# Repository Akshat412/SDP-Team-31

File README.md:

# SDP-Team-31
SDP23 Project for Team 31

We present SMH, a smart biking helmet and associated sensing system which can sense riders’ vital signs such as heart rate, ambient temperature and humidity, and make it accessible to them while they bike. In the event of an accident, the system would send a remote alert to a registered contact, including the rider’s location. The helmet uses a microcontroller for sampling a MEMS accelerometer capable of measuring upto 200 Gs of acceleration at 4 KHz for collision detection. In the event of a dangerous collision, the system communicates with an Android app over Bluetooth Low Energy, which then sends a text message to an emergency contact. The bike board samples temperature, humidity, heart rate, altitude and UV-index and displays them to the biker during their bike ride. Both devices are lightweight, inexpensive, and have long battery lives. 

Members: 
Marloon Paula Gonzalez - EE 2023; 
Max Morel - EE 2023; 
Ruchit Patel - EE 2023; 
Akshat Sahay - CompE 2023; 

This repository contains the hardware and software for the helmet board which performs concussion detection and generates BLE alerts for the associated smartphone app in case of a dangerous collision. Software is written using the RP2040 core in Arduino, with the Adafruit BLE Friend library to interface with the BLE module. The hardware is designed in KiCad 7.

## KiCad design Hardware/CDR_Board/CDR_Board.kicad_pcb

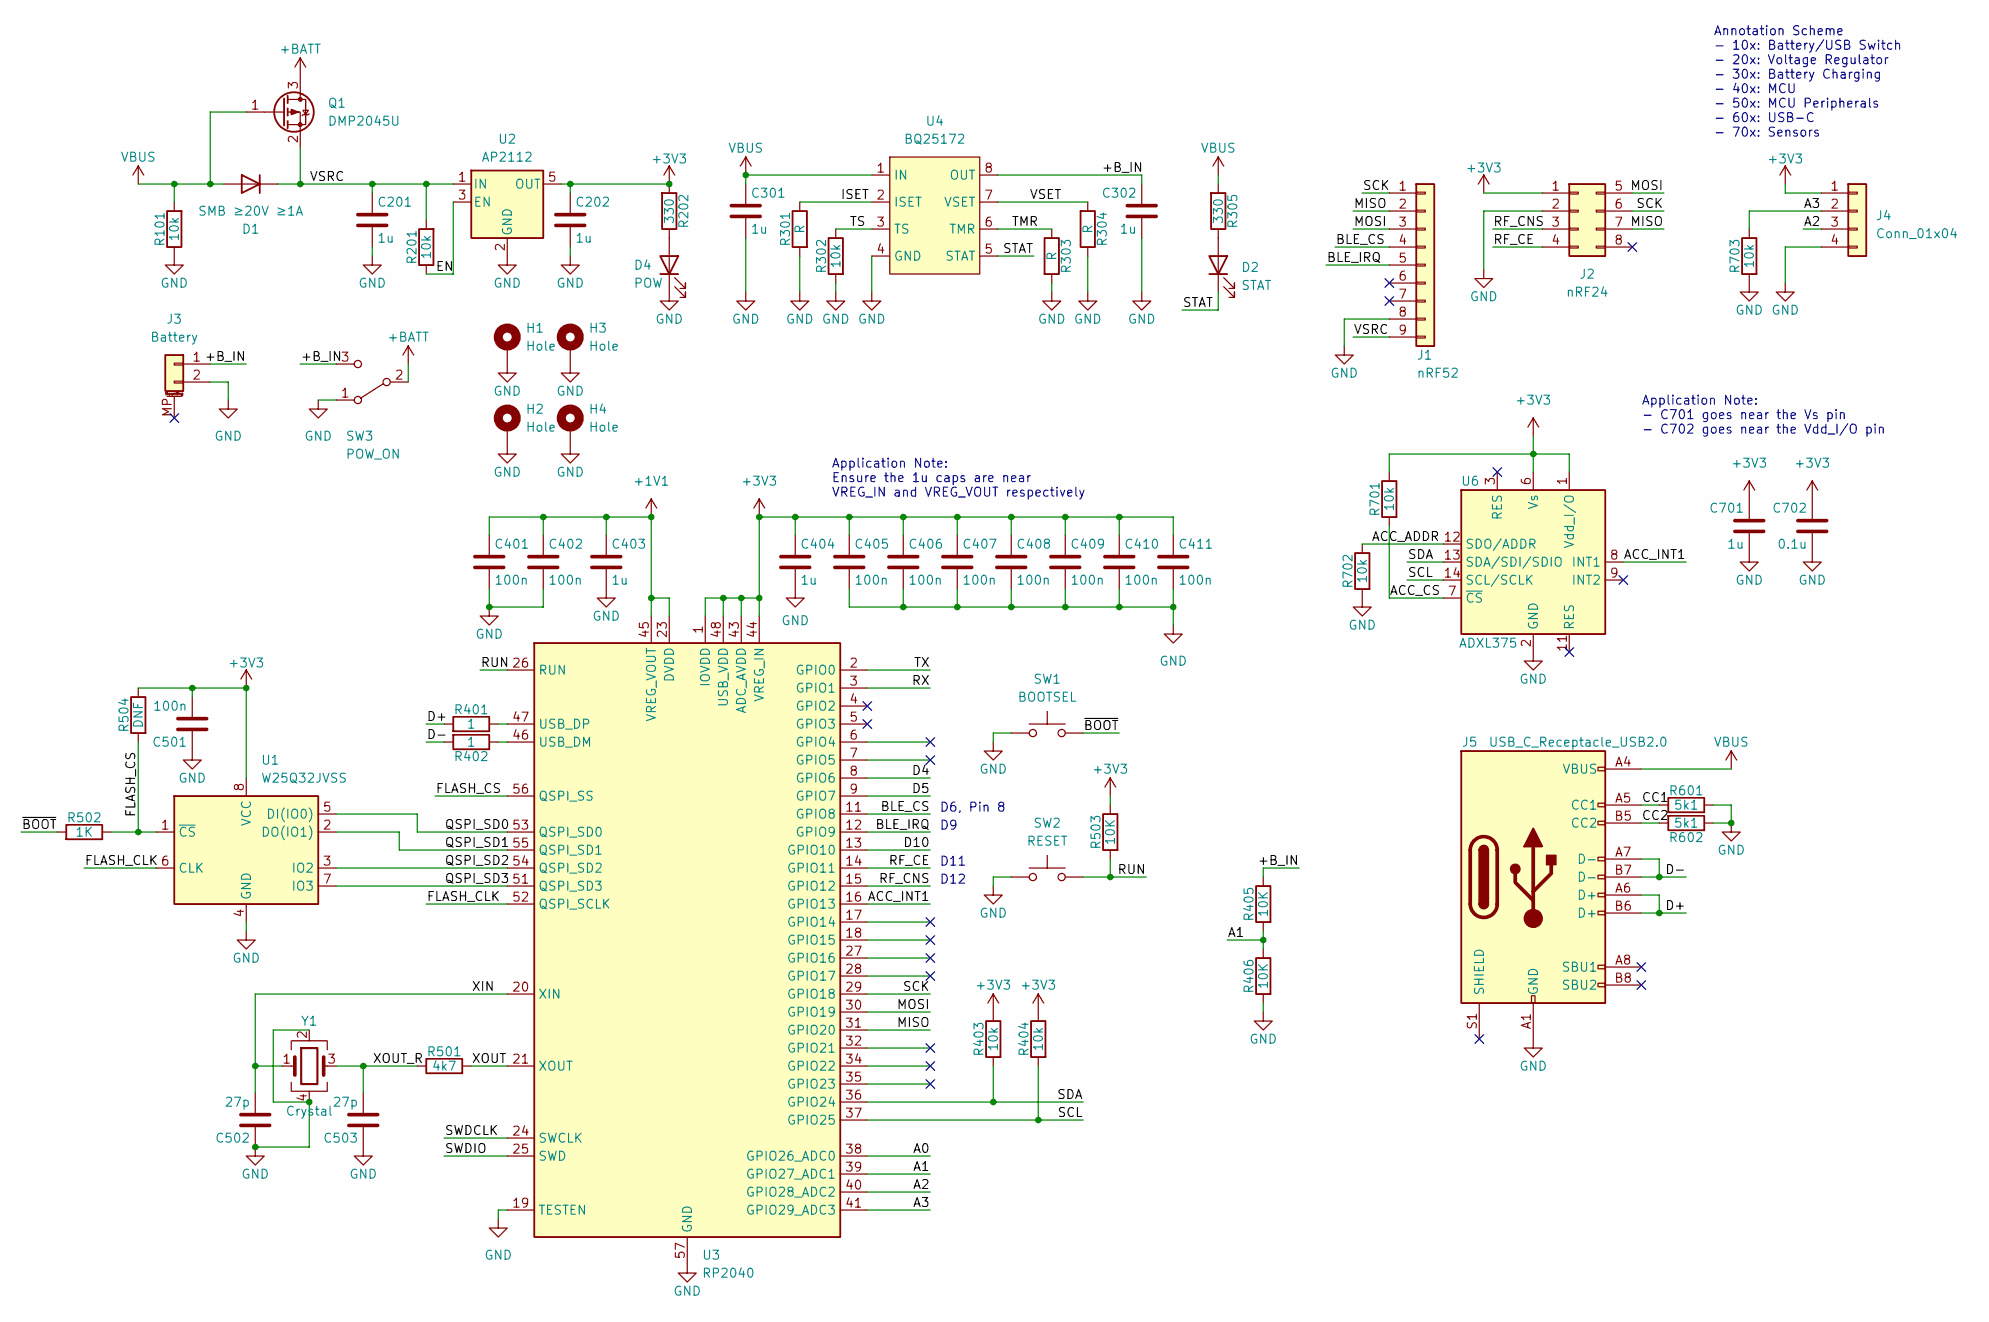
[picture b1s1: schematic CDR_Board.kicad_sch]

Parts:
C201, C202, C301, C302, C701: 1u; C_0805_2012Metric_Pad1.18x1.45mm_HandSolder
C401, C402, C405, C406, C407, C408, C409, C410, C411: 100n; C_0603_1608Metric_Pad1.08x0.95mm_HandSolder
C403, C404: 1u; C_0603_1608Metric_Pad1.08x0.95mm_HandSolder
C501: 100n; C_0805_2012Metric_Pad1.18x1.45mm_HandSolder
C502, C503: 27p; C_0805_2012Metric_Pad1.18x1.45mm_HandSolder
C702: 0.1u; C_0805_2012Metric_Pad1.18x1.45mm_HandSolder
D1: SMB ≥20V ≥1A; D_SOD-323_HandSoldering
D2: STAT; LED_0805_2012Metric_Pad1.15x1.40mm_HandSolder
D4: POW; LED_0805_2012Metric_Pad1.15x1.40mm_HandSolder
H1, H2, H3, H4: Hole; MountingHole_2.2mm_M2_DIN965_Pad
J1: nRF52; PinSocket_1x09_P2.54mm_Vertical
J2: nRF24; PinSocket_2x04_P2.54mm_Vertical
J3: Battery; JST_PH_S2B-PH-SM4-TB_1x02-1MP_P2.00mm_Horizontal
J4: Conn_01x04; PinSocket_1x04_P2.54mm_Vertical
J5: USB_C_Receptacle_USB2.0; USB_C_Receptacle_Palconn_UTC16-G
Q1: DMP2045U; SOT-23
R101, R201, R302, R403, R404, R701, R702, R703: 10k; R_0805_2012Metric_Pad1.20x1.40mm_HandSolder
R202, R305: 330; R_0805_2012Metric_Pad1.20x1.40mm_HandSolder
R301, R303, R304: R; R_0805_2012Metric_Pad1.20x1.40mm_HandSolder
R401, R402: 1; R_0805_2012Metric_Pad1.20x1.40mm_HandSolder
R405, R406, R503: 10K; R_0805_2012Metric_Pad1.20x1.40mm_HandSolder
R501: 4k7; R_0805_2012Metric_Pad1.20x1.40mm_HandSolder
R502: 1K; R_0805_2012Metric_Pad1.20x1.40mm_HandSolder
R504: DNF; R_0805_2012Metric_Pad1.20x1.40mm_HandSolder
R601, R602: 5k1; R_0805_2012Metric_Pad1.20x1.40mm_HandSolder
SW1: BOOTSEL; SW_Push_1P1T_NO_CK_KMR2
SW2: RESET; SW_Push_1P1T_NO_CK_KMR2
SW3: POW_ON; E-Switch-EG1218
U1: W25Q32JVSS; SOIC-8_5.23x5.23mm_P1.27mm
U2: AP2112; SOT-23-5
U3: RP2040; QFN-56-1EP_7x7mm_P0.4mm_EP3.2x3.2mm
U4: BQ25172; WSON-8-1EP_2x2mm_P0.5mm_EP0.9x1.6mm_ThermalVias
U6: ADXL375; LGA-14_3x5mm_P0.8mm_LayoutBorder1x6y
Y1: Crystal; Crystal_SMD_SeikoEpson_FA238-4Pin_3.2x2.5mm

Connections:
+1V1: C401.1, C402.1, C403.1, U3.23 (DVDD), U3.45 (VREG_VOUT), U3.50 (DVDD)
+3V3: C202.1, C404.1, C405.1, C406.1, C407.1, C408.1, C409.1, C410.1, C411.1, C501.2, C701.1, C702.1, J2.1, J4.1, R202.2, R403.1, R404.1, R503.1, R504.1, R701.1, U1.8 (VCC), U2.5 (OUT), U3.1 (IOVDD), U3.10 (IOVDD), U3.22 (IOVDD), U3.33 (IOVDD), U3.42 (IOVDD), U3.43 (ADC_AVDD), U3.44 (VREG_IN), U3.48 (USB_VDD), U3.49 (IOVDD), U6.1 (Vdd_I/O), U6.6 (Vs)
+BATT: Q1.3 (D), SW3.2 (B)
/+B_IN: C302.1, J3.1, R405.1, SW3.3 (C), U4.8 (OUT)
/A0: U3.38 (GPIO26_ADC0)
/A1: R405.2, R406.1, U3.39 (GPIO27_ADC1)
/A2: J4.3, U3.40 (GPIO28_ADC2)
/A3: J4.2, R703.1, U3.41 (GPIO29_ADC3)
/ACC_ADDR: R702.1, U6.12 (SDO/ADDR)
/ACC_CS: R701.2, U6.7 (~CS)
/ACC_INT1: U3.16 (GPIO13), U6.8 (INT1)
/BLE_CS: J1.4, U3.11 (GPIO8)
/BLE_IRQ: J1.5, U3.12 (GPIO9)
/CC1: J5.A5 (CC1), R601.2
/CC2: J5.B5 (CC2), R602.2
/D4: U3.8 (GPIO6)
/D5: U3.9 (GPIO7)
/D10: U3.13 (GPIO10)
/D+: J5.A6 (D+), J5.B6 (D+), R401.2
/D-: J5.A7 (D-), J5.B7 (D-), R402.2
/EN: R201.1, U2.3 (EN)
/FLASH_CLK: U1.6 (CLK), U3.52 (QSPI_SCLK)
/FLASH_CS: R502.1, R504.2, U1.1 (~CS), U3.56 (QSPI_SS)
/ISET: R301.1, U4.2 (ISET)
/MISO: J1.2, J2.7, U3.31 (GPIO20)
/MOSI: J1.3, J2.5, U3.30 (GPIO19)
/QSPI_SD0: U1.5 (DI(IO0)), U3.53 (QSPI_SD0)
/QSPI_SD1: U1.2 (DO(IO1)), U3.55 (QSPI_SD1)
/QSPI_SD2: U1.3 (IO2), U3.54 (QSPI_SD2)
/QSPI_SD3: U1.7 (IO3), U3.51 (QSPI_SD3)
/RF_CE: J2.4, U3.14 (GPIO11)
/RF_CNS: J2.3, U3.15 (GPIO12)
/RUN: R503.2, SW2.2, U3.26 (RUN)
/RX: U3.3 (GPIO1)
/SCK: J1.1, J2.6, U3.29 (GPIO18)
/SCL: R404.2, U3.37 (GPIO25), U6.14 (SCL/SCLK)
/SDA: R403.2, U3.36 (GPIO24), U6.13 (SDA/SDI/SDIO)
/STAT: D2.1 (K), U4.5 (STAT)
/SWDCLK: U3.24 (SWCLK)
/SWDIO: U3.25 (SWD)
/TMR: R303.1, U4.6 (TMR)
/TS: R302.1, U4.3 (TS)
/TX: U3.2 (GPIO0)
/VSET: R304.2, U4.7 (VSET)
/VSRC: C201.1, D1.1 (K), J1.9, Q1.2 (S), R201.2, U2.1 (IN)
/XIN: C502.2, U3.20 (XIN), Y1.1
/XOUT: R501.2, U3.21 (XOUT)
/XOUT_R: C503.2, R501.1, Y1.3
/~BOOT: R502.2, SW1.2
GND: C201.2, C202.2, C301.2, C302.2, C401.2, C402.2, C403.2, C404.2, C405.2, C406.2, C407.2, C408.2, C409.2, C410.2, C411.2, C501.1, C502.1, C503.1, C701.2, C702.2, D4.1 (K), H1.1, H2.1, H3.1, H4.1, J1.8, J2.2, J3.2, J4.4, J5.A1 (GND), J5.A12 (GND), J5.B1 (GND), J5.B12 (GND), R101.1, R301.2, R302.2, R303.2, R304.1, R406.2, R601.1, R602.1, R702.2, R703.2, SW1.1, SW2.1, SW3.1 (A), U1.4 (GND), U2.2 (GND), U3.19 (TESTEN), U3.57 (GND), U4.4 (GND), U6.2 (GND), U6.4 (GND), U6.5 (GND), Y1.2, Y1.4
unnamed: D2.2 (A), R305.1
unnamed: D4.2 (A), R202.1
unnamed: R402.1, U3.46 (USB_DM)
unnamed: R401.1, U3.47 (USB_DP)
VBUS: C301.1, D1.2 (A), J5.A4 (VBUS), J5.A9 (VBUS), J5.B4 (VBUS), J5.B9 (VBUS), Q1.1 (G), R101.2, R305.2, U4.1 (IN)

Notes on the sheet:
D6, Pin 8
Annotation Scheme - 10x: Battery/USB Switch - 20x: Voltage Regulator - 30x: Battery Charging - 40x: MCU - 50x: MCU Peripherals - 60x: USB-C - 70x: Sensors
Application Note: Ensure the 1u caps are near VREG_IN and VREG_VOUT respectively
D11
Application Note: - C701 goes near the Vs pin - C702 goes near the Vdd_I/O pin
D12

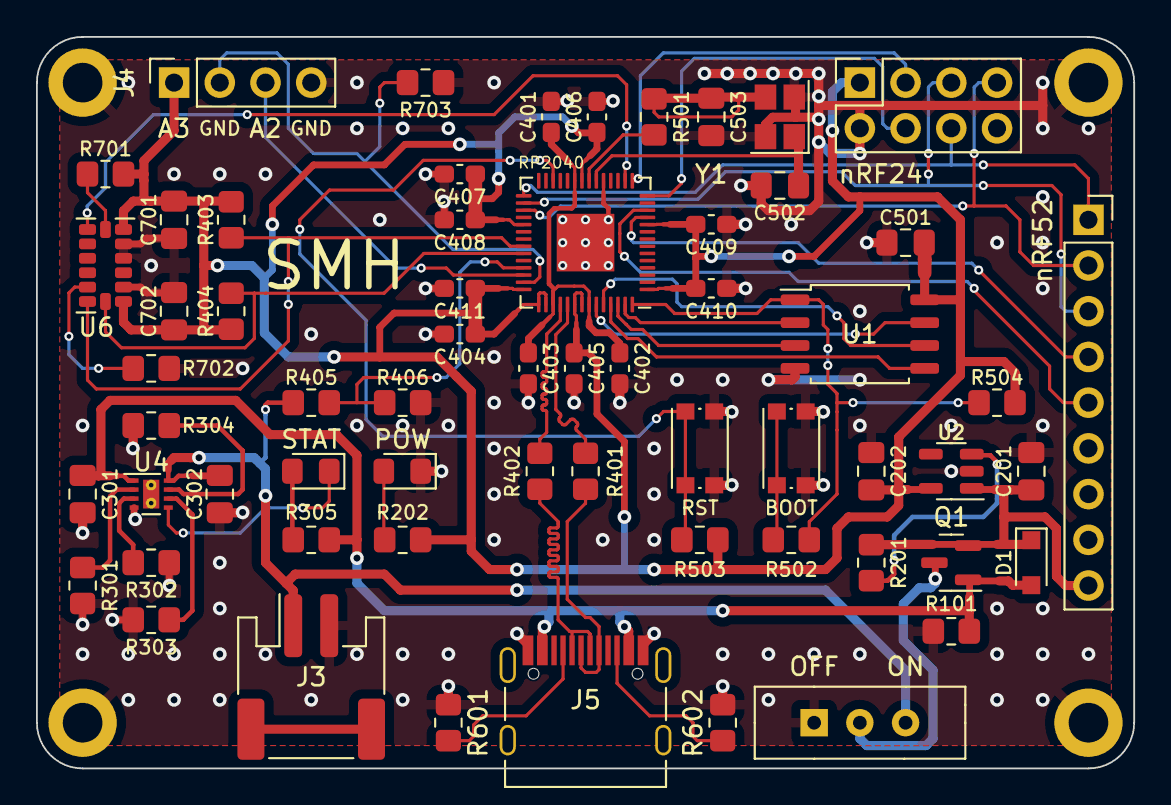
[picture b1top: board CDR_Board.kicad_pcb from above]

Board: 2 copper layers, 61.0 x 40.6 mm, 65 parts (0 on the bottom side), 47 nets.

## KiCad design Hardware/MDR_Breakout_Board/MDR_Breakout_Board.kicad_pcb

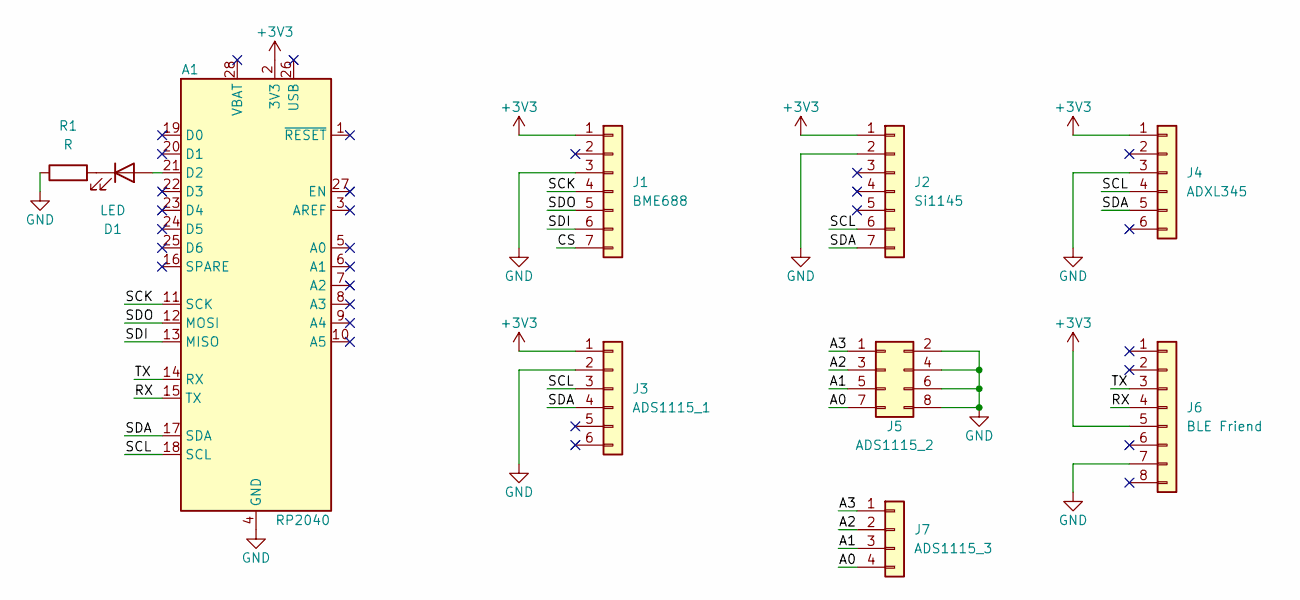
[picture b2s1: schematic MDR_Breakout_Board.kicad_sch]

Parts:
A1: RP2040; Adafruit_Feather
D1: LED; LED_D5.0mm
J1: BME688; PinSocket_1x07_P2.54mm_Vertical
J2: Si1145; PinSocket_1x07_P2.54mm_Vertical
J3: ADS1115_1; PinSocket_1x06_P2.54mm_Vertical
J4: ADXL345; PinSocket_1x06_P2.54mm_Vertical
J5: ADS1115_2; PinSocket_2x04_P2.54mm_Vertical
J6: BLE Friend; PinSocket_1x08_P2.54mm_Vertical
J7: ADS1115_3; PinSocket_1x04_P2.54mm_Vertical
R1: R; R_Axial_DIN0309_L9.0mm_D3.2mm_P12.70mm_Horizontal

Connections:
+3V3: A1.2 (3V3), J1.1, J2.1, J3.1, J4.1, J6.5
/A0: J5.7, J7.4
/A1: J5.5, J7.3
/A2: J5.3, J7.2
/A3: J5.1, J7.1
/CS: J1.7
/RX: A1.15 (TX), J6.4
/SCK: A1.11 (SCK), J1.4
/SCL: A1.18 (SCL), J2.6, J3.3, J4.4
/SDA: A1.17 (SDA), J2.7, J3.4, J4.5
/SDI: A1.13 (MISO), J1.6
/SDO: A1.12 (MOSI), J1.5
/TX: A1.14 (RX), J6.3
GND: A1.4 (GND), J1.3, J2.2, J3.2, J4.3, J5.2, J5.4, J5.6, J5.8, J6.7, R1.1
unnamed: A1.21 (D2), D1.2 (A)
unnamed: D1.1 (K), R1.2

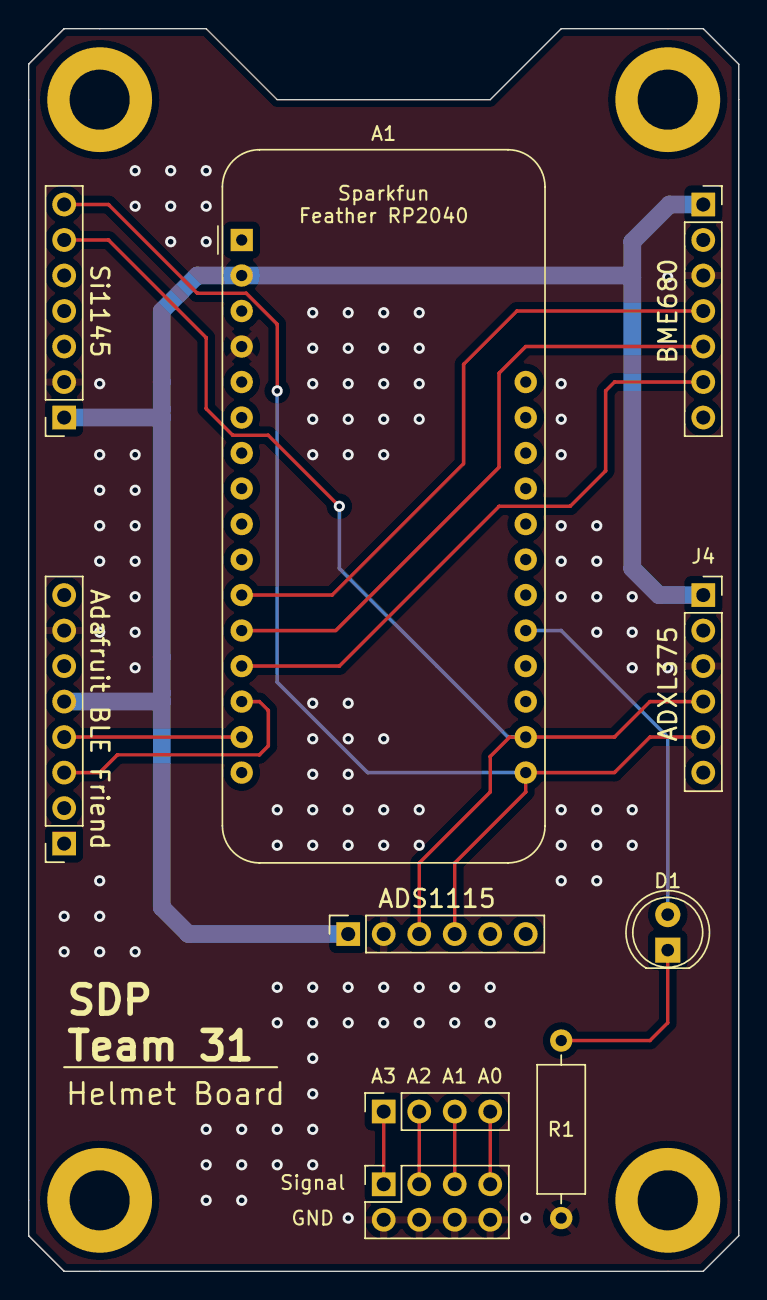
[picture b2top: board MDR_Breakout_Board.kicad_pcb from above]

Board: 2 copper layers, 50.8 x 88.9 mm, 10 parts (0 on the bottom side), 15 nets.

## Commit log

2022-10-28 Added MDR PCB files
    Added MDR PCB files, started schematic
2022-11-01 Added MDR Breakout PCB
2022-11-01 MDR PCB: Added some stitching vias
2022-11-21 Updated helmet code, test CSVs
2022-12-06 Updated Testing Code
    Testing code for all systems
2022-12-09 Finalized MDR System Software
2023-01-07 CDR Board Component Placement
    Component placement on 50 mil grid.
2023-01-08 CDR Board Placement Revision
    Some things on 25 mil grid, 0603 capacitors for RP2040 decoupling.
2023-01-13 Added critical traces
2023-01-22 Finished all routing
2023-01-28 Added stitching vias
2023-02-02 Added more stitching vias
2023-02-12 Finalized PCB v1
2023-02-20 Updated helmet PCB
2023-03-01 Added CDR helmet code
2023-03-22 Added pullup/pulldown resistors for IMU
    Added pullup resistor for CS, pulldown resistor for ADDR pin of IMU. Moved silkscreen
2023-03-28 Updated bike firmware, testing
2023-03-29 Collected collision data
2023-04-17 Updated helmet PCB
    Added voltage divider for battery measurement, pull-down resistor for FSR measurement
2023-04-18 Updated ADXL375 I2C, helmet PCB
2023-04-24 Working I2C drivers
2023-05-05 FPR System Software
    Finished software for FPR helmet
